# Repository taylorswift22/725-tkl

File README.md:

725-tkl

If you intend to have this produced, please contact me on discord "tamsin." because there are some small adjustments I should make.

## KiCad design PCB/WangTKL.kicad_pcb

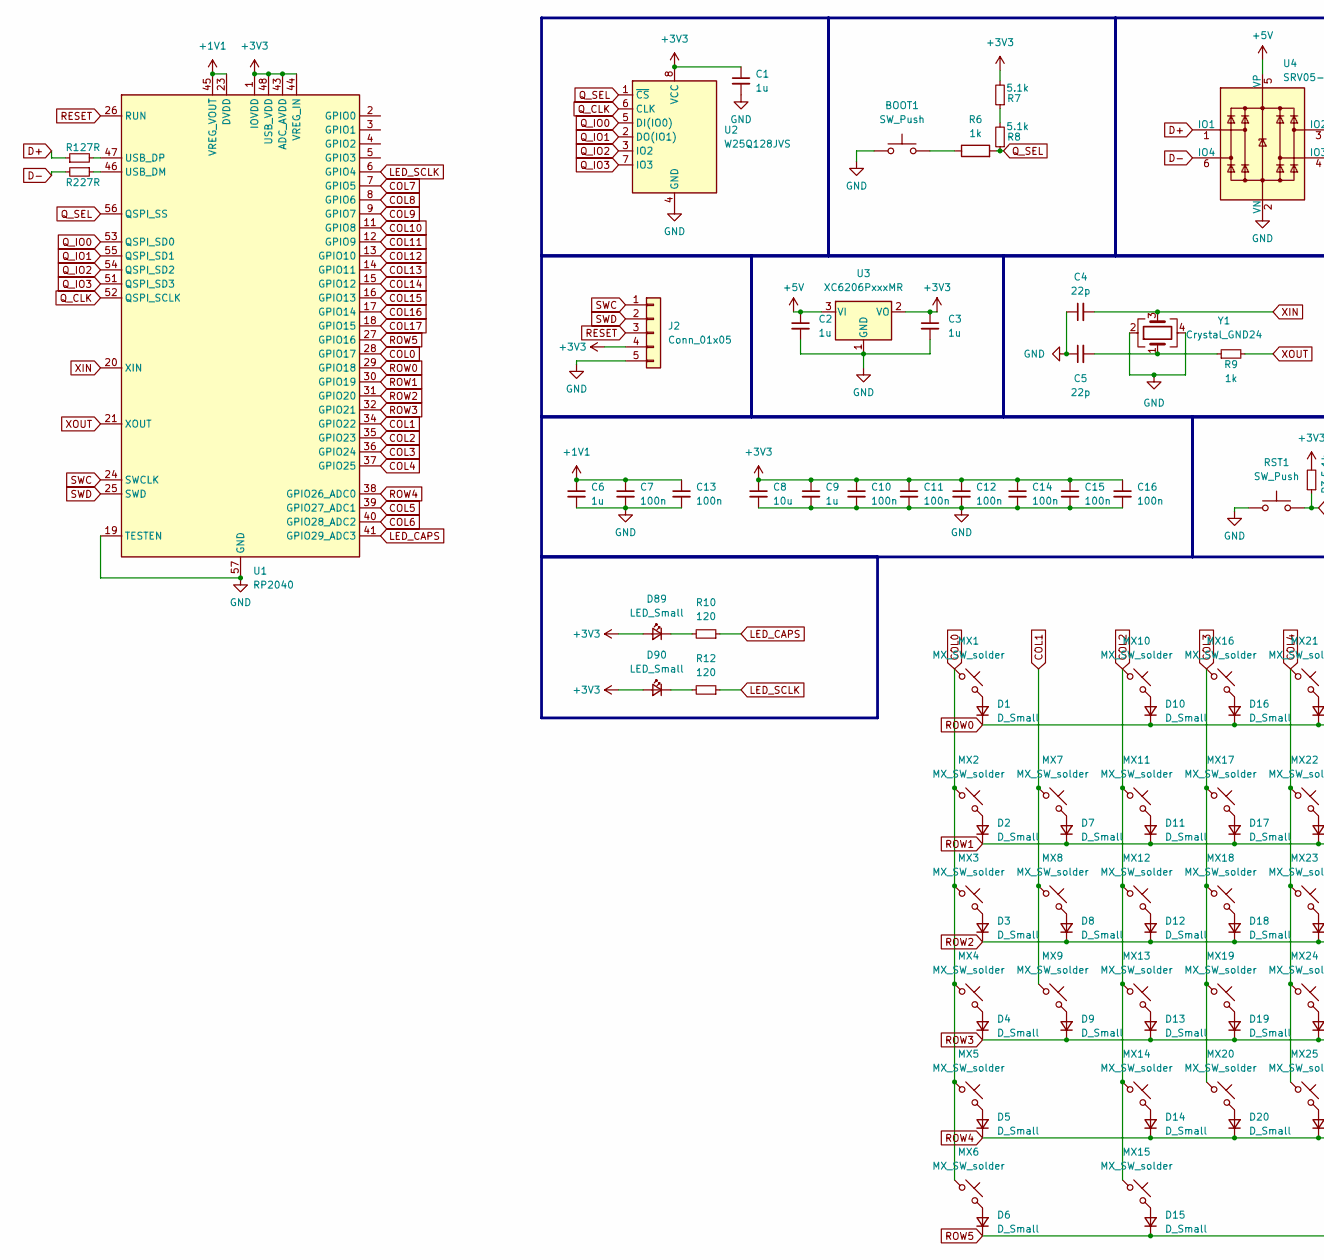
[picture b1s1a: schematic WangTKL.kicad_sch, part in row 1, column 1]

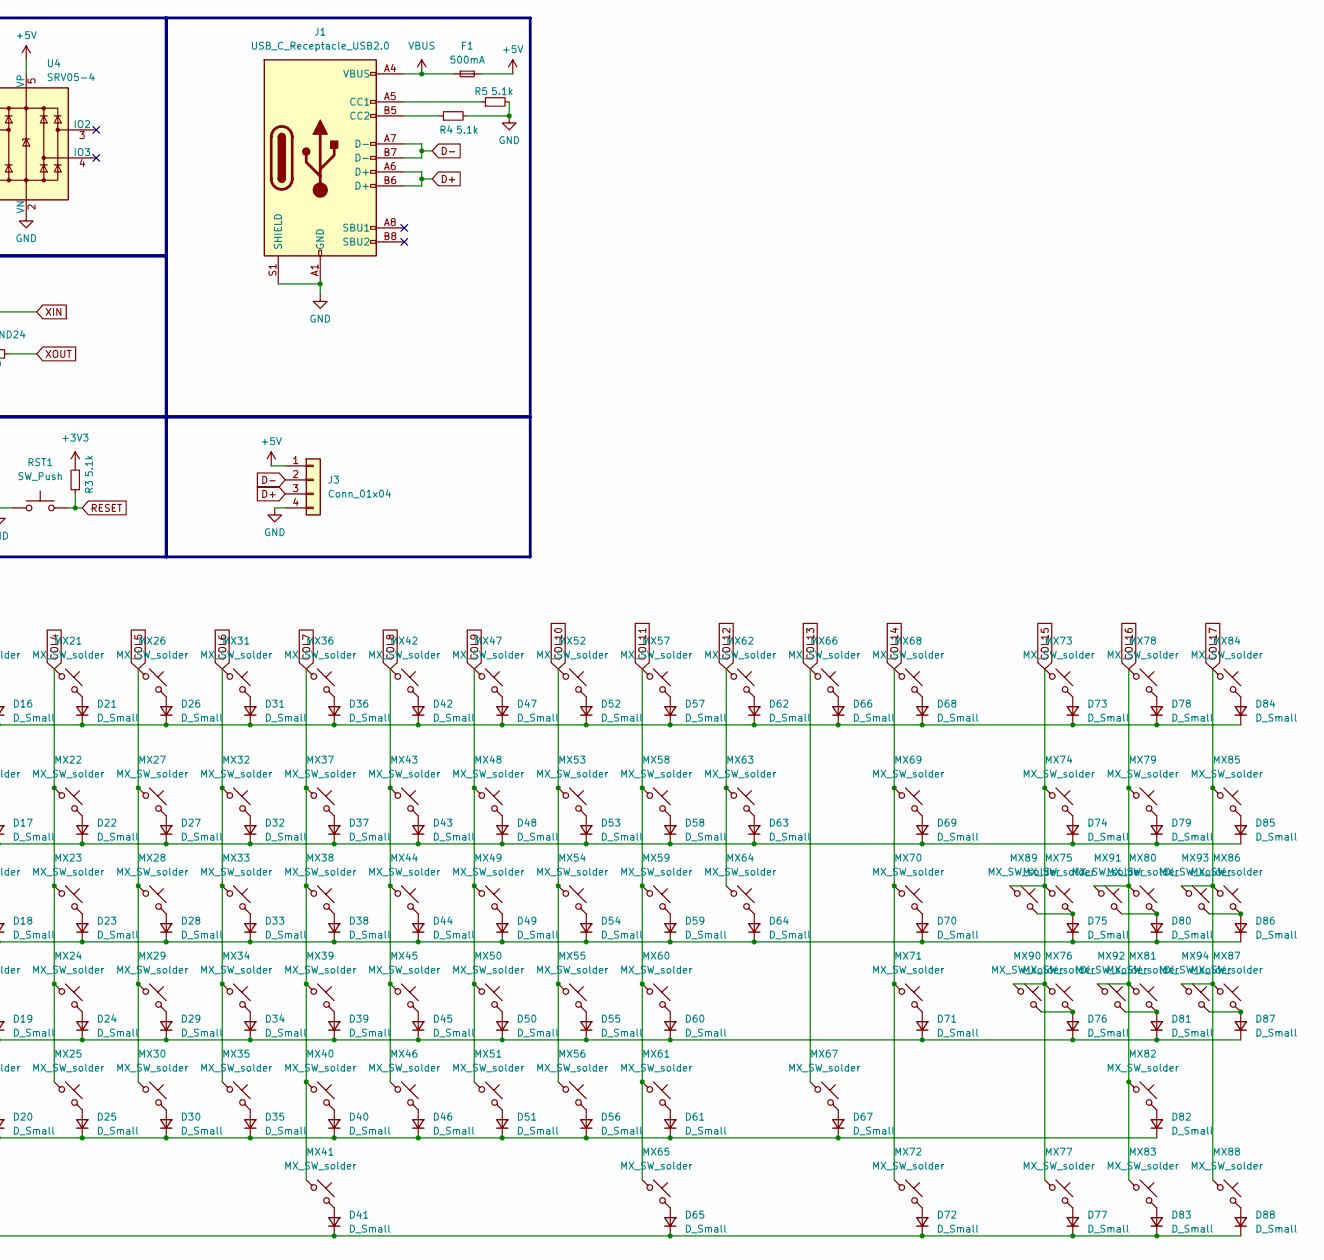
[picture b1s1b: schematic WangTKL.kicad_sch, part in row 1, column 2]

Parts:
BOOT1: SW_Push; SW_SPST_TL3342
C1, C2, C3, C6, C9: 1u; C_0402_1005Metric
C4, C5: 22p; C_0402_1005Metric
C7, C10, C11, C12, C13, C14, C15, C16: 100n; C_0402_1005Metric
C8: 10u; C_0603_1608Metric
D1, D2, D3, D4, D5, D6, D7, D8, D9, D10, D11, D12, D13, D14, D15, D16, D17, D18, D19, D20, D21, D22, D23, D24, D25, D26, D27, D28, D29, D30, D31, D32, D33, D34, D35, D36, D37, D38, D39, D40, D41, D42, D43, D44, D45, D46, D47, D48, D49, D50, D51, D52, D53, D54, D55, D56, D57, D58, D59, D60, D61, D62, D63, D64, D65, D66, D67, D68, D69, D70, D71, D72, D73, D74, D75, D76, D77, D78, D79, D80, D81, D82, D83, D84, D85, D86, D87, D88: D_Small; D_SOD-123
D89, D90: LED_Small; PinHeader_1x02_P2.54mm_Horizontal
F1: 500mA; Fuse_1206_3216Metric
J1: USB_C_Receptacle_USB2.0; USB_C_Receptacle_HRO_TYPE-C-31-M-12
J2: Conn_01x05; PinHeader_1x05_P2.54mm_Vertical
J3: Conn_01x04; Molex_Pico-EZmate_78171-0004_1x04-1MP_P1.20mm_Vertical
MX1, MX2, MX3, MX4, MX5, MX6, MX7, MX8, MX9, MX10, MX11, MX12, MX13, MX14, MX15, MX16, MX17, MX18, MX19, MX20, MX21, MX22, MX23, MX24, MX25, MX26, MX27, MX28, MX29, MX30, MX31, MX32, MX33, MX34, MX35, MX36, MX37, MX38, MX39, MX40, MX41, MX42, MX43, MX44, MX45, MX46, MX47, MX48, MX49, MX50, MX51, MX52, MX53, MX54, MX55, MX56, MX57, MX58, MX59, MX60, MX61, MX62, MX63, MX64, MX65, MX66, MX67, MX68, MX69, MX70, MX71, MX72, MX73, MX74, MX75, MX76, MX77, MX78, MX79, MX80, MX81, MX82, MX83, MX84, MX85, MX86, MX87, MX88, MX89, MX90, MX91, MX92, MX93, MX94: MX_SW_solder; SW_Alps_1u
R1, R2: 27R; R_0402_1005Metric
R3, R4, R5, R7, R8: 5.1k; R_0402_1005Metric
R6, R9: 1k; R_0402_1005Metric
R10, R12: 120; R_0402_1005Metric
RST1: SW_Push; SW_SPST_TL3342
U1: RP2040; QFN-56-1EP_7x7mm_P0.4mm_EP3.2x3.2mm
U2: W25Q128JVS; SOIC-8_5.23x5.23mm_P1.27mm
U3: XC6206PxxxMR; SOT-23-3
U4: SRV05-4; SOT-23-6-routable
Y1: Crystal_GND24; Crystal_SMD_3225-4Pin_3.2x2.5mm

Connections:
+1V1: C6.1, C7.1, C13.1, U1.23 (DVDD), U1.45 (VREG_VOUT), U1.50 (DVDD)
+3V3: C1.1, C3.1, C8.1, C9.1, C10.1, C11.1, C12.1, C14.1, C15.1, C16.1, D89.2 (A), D90.2 (A), J2.4, R3.2, R7.2, U1.1 (IOVDD), U1.10 (IOVDD), U1.22 (IOVDD), U1.33 (IOVDD), U1.42 (IOVDD), U1.43 (ADC_AVDD), U1.44 (VREG_IN), U1.48 (USB_VDD), U1.49 (IOVDD), U2.8 (VCC), U3.2 (VO)
+5V: C2.1, F1.2, J3.1, U3.3 (VI), U4.5 (VP)
COL0: MX1.1, MX2.1, MX3.1, MX4.1, MX5.1, MX6.1, U1.28 (GPIO17)
COL1: MX7.1, MX8.1, MX9.1, U1.34 (GPIO22)
COL2: MX10.1, MX11.1, MX12.1, MX13.1, MX14.1, MX15.1, U1.35 (GPIO23)
COL3: MX16.1, MX17.1, MX18.1, MX19.1, MX20.1, U1.36 (GPIO24)
COL4: MX21.1, MX22.1, MX23.1, MX24.1, MX25.1, U1.37 (GPIO25)
COL5: MX26.1, MX27.1, MX28.1, MX29.1, MX30.1, U1.39 (GPIO27_ADC1)
COL6: MX31.1, MX32.1, MX33.1, MX34.1, MX35.1, U1.40 (GPIO28_ADC2)
COL7: MX36.1, MX37.1, MX38.1, MX39.1, MX40.1, MX41.1, U1.7 (GPIO5)
COL8: MX42.1, MX43.1, MX44.1, MX45.1, MX46.1, U1.8 (GPIO6)
COL9: MX47.1, MX48.1, MX49.1, MX50.1, MX51.1, U1.9 (GPIO7)
COL10: MX52.1, MX53.1, MX54.1, MX55.1, MX56.1, U1.11 (GPIO8)
COL11: MX57.1, MX58.1, MX59.1, MX60.1, MX61.1, MX65.1, U1.12 (GPIO9)
COL12: MX62.1, MX63.1, MX64.1, U1.13 (GPIO10)
COL13: MX66.1, MX67.1, U1.14 (GPIO11)
COL14: MX68.1, MX69.1, MX70.1, MX71.1, MX72.1, U1.15 (GPIO12)
COL15: MX73.1, MX74.1, MX75.1, MX76.1, MX77.1, MX89.1, MX90.1, U1.16 (GPIO13)
COL16: MX78.1, MX79.1, MX80.1, MX81.1, MX82.1, MX83.1, MX91.1, MX92.1, U1.17 (GPIO14)
COL17: MX84.1, MX85.1, MX86.1, MX87.1, MX88.1, MX93.1, MX94.1, U1.18 (GPIO15)
D+: J1.A6 (D+), J1.B6 (D+), J3.3, R1.1, U4.1 (IO1)
D-: J1.A7 (D-), J1.B7 (D-), J3.2, R2.2, U4.6 (IO4)
GND: BOOT1.1, C1.2, C2.2, C3.2, C4.1, C5.1, C6.2, C7.2, C8.2, C9.2, C10.2, C11.2, C12.2, C13.2, C14.2, C15.2, C16.2, J1.A1 (GND), J1.A12 (GND), J1.B1 (GND), J1.B12 (GND), J1.S1 (SHIELD), J2.5, J3.4, R4.2, R5.2, RST1.1, U1.19 (TESTEN), U1.57 (GND), U2.4 (GND), U3.1 (GND), U4.2 (VN), Y1.2, Y1.4
LED_CAPS: R10.1, U1.41 (GPIO29_ADC3)
LED_SCLK: R12.1, U1.6 (GPIO4)
unnamed: BOOT1.2, R6.1
unnamed: C5.2, R9.1, Y1.1
unnamed: D1.2 (A), MX1.2
unnamed: D2.2 (A), MX2.2
unnamed: D3.2 (A), MX3.2
unnamed: D4.2 (A), MX4.2
unnamed: D5.2 (A), MX5.2
unnamed: D6.2 (A), MX6.2
unnamed: D7.2 (A), MX7.2
unnamed: D8.2 (A), MX8.2
unnamed: D9.2 (A), MX9.2
unnamed: D10.2 (A), MX10.2
unnamed: D11.2 (A), MX11.2
unnamed: D12.2 (A), MX12.2
unnamed: D13.2 (A), MX13.2
unnamed: D14.2 (A), MX14.2
unnamed: D15.2 (A), MX15.2
unnamed: D16.2 (A), MX16.2
unnamed: D17.2 (A), MX17.2
unnamed: D18.2 (A), MX18.2
unnamed: D19.2 (A), MX19.2
unnamed: D20.2 (A), MX20.2
unnamed: D21.2 (A), MX21.2
unnamed: D22.2 (A), MX22.2
unnamed: D23.2 (A), MX23.2
unnamed: D24.2 (A), MX24.2
unnamed: D25.2 (A), MX25.2
unnamed: D26.2 (A), MX26.2
unnamed: D27.2 (A), MX27.2
unnamed: D28.2 (A), MX28.2
unnamed: D29.2 (A), MX29.2
unnamed: D30.2 (A), MX30.2
unnamed: D31.2 (A), MX31.2
unnamed: D32.2 (A), MX32.2
unnamed: D33.2 (A), MX33.2
unnamed: D34.2 (A), MX34.2
unnamed: D35.2 (A), MX35.2
unnamed: D36.2 (A), MX36.2
unnamed: D37.2 (A), MX37.2
unnamed: D38.2 (A), MX38.2
unnamed: D39.2 (A), MX39.2
unnamed: D40.2 (A), MX40.2
unnamed: D41.2 (A), MX41.2
unnamed: D42.2 (A), MX42.2
unnamed: D43.2 (A), MX43.2
unnamed: D44.2 (A), MX44.2
unnamed: D45.2 (A), MX45.2
unnamed: D46.2 (A), MX46.2
unnamed: D47.2 (A), MX47.2
unnamed: D48.2 (A), MX48.2
unnamed: D49.2 (A), MX49.2
unnamed: D50.2 (A), MX50.2
unnamed: D51.2 (A), MX51.2
unnamed: D52.2 (A), MX52.2
unnamed: D53.2 (A), MX53.2
unnamed: D54.2 (A), MX54.2
unnamed: D55.2 (A), MX55.2
unnamed: D56.2 (A), MX56.2
unnamed: D57.2 (A), MX57.2
unnamed: D58.2 (A), MX58.2
unnamed: D59.2 (A), MX59.2
unnamed: D60.2 (A), MX60.2
unnamed: D61.2 (A), MX61.2
unnamed: D62.2 (A), MX62.2
unnamed: D63.2 (A), MX63.2
unnamed: D64.2 (A), MX64.2
unnamed: D65.2 (A), MX65.2
unnamed: D66.2 (A), MX66.2
unnamed: D67.2 (A), MX67.2
unnamed: D68.2 (A), MX68.2
unnamed: D69.2 (A), MX69.2
unnamed: D70.2 (A), MX70.2
unnamed: D71.2 (A), MX71.2
unnamed: D72.2 (A), MX72.2
unnamed: D73.2 (A), MX73.2
unnamed: D74.2 (A), MX74.2
unnamed: D75.2 (A), MX75.2, MX89.2
unnamed: D76.2 (A), MX76.2, MX90.2
unnamed: D77.2 (A), MX77.2
unnamed: D78.2 (A), MX78.2
unnamed: D79.2 (A), MX79.2
unnamed: D80.2 (A), MX80.2, MX91.2
unnamed: D81.2 (A), MX81.2, MX92.2
unnamed: D82.2 (A), MX82.2
unnamed: D83.2 (A), MX83.2
unnamed: D84.2 (A), MX84.2
unnamed: D85.2 (A), MX85.2
unnamed: D86.2 (A), MX86.2, MX93.2
unnamed: D87.2 (A), MX87.2, MX94.2
unnamed: D88.2 (A), MX88.2
unnamed: D89.1 (K), R10.2
unnamed: D90.1 (K), R12.2
unnamed: J1.A5 (CC1), R5.1
unnamed: J1.B5 (CC2), R4.1
unnamed: R7.1, R8.2
unnamed: R2.1, U1.46 (USB_DM)
unnamed: R1.2, U1.47 (USB_DP)
Q_CLK: U1.52 (QSPI_SCLK), U2.6 (CLK)
Q_IO0: U1.53 (QSPI_SD0), U2.5 (DI(IO0))
Q_IO1: U1.55 (QSPI_SD1), U2.2 (DO(IO1))
Q_IO2: U1.54 (QSPI_SD2), U2.3 (IO2)
Q_IO3: U1.51 (QSPI_SD3), U2.7 (IO3)
Q_SEL: R6.2, R8.1, U1.56 (QSPI_SS), U2.1 (~CS)
RESET: J2.3, R3.1, RST1.2, U1.26 (RUN)
ROW0: D1.1 (K), D10.1 (K), D16.1 (K), D21.1 (K), D26.1 (K), D31.1 (K), D36.1 (K), D42.1 (K), D47.1 (K), D52.1 (K), D57.1 (K), D62.1 (K), D66.1 (K), D68.1 (K), D73.1 (K), D78.1 (K), D84.1 (K), U1.29 (GPIO18)
ROW1: D2.1 (K), D7.1 (K), D11.1 (K), D17.1 (K), D22.1 (K), D27.1 (K), D32.1 (K), D37.1 (K), D43.1 (K), D48.1 (K), D53.1 (K), D58.1 (K), D63.1 (K), D69.1 (K), D74.1 (K), D79.1 (K), D85.1 (K), U1.30 (GPIO19)
ROW2: D3.1 (K), D8.1 (K), D12.1 (K), D18.1 (K), D23.1 (K), D28.1 (K), D33.1 (K), D38.1 (K), D44.1 (K), D49.1 (K), D54.1 (K), D59.1 (K), D64.1 (K), D70.1 (K), D75.1 (K), D80.1 (K), D86.1 (K), U1.31 (GPIO20)
ROW3: D4.1 (K), D9.1 (K), D13.1 (K), D19.1 (K), D24.1 (K), D29.1 (K), D34.1 (K), D39.1 (K), D45.1 (K), D50.1 (K), D55.1 (K), D60.1 (K), D71.1 (K), D76.1 (K), D81.1 (K), D87.1 (K), U1.32 (GPIO21)
ROW4: D5.1 (K), D14.1 (K), D20.1 (K), D25.1 (K), D30.1 (K), D35.1 (K), D40.1 (K), D46.1 (K), D51.1 (K), D56.1 (K), D61.1 (K), D67.1 (K), D82.1 (K), U1.38 (GPIO26_ADC0)
ROW5: D6.1 (K), D15.1 (K), D41.1 (K), D65.1 (K), D72.1 (K), D77.1 (K), D83.1 (K), D88.1 (K), U1.27 (GPIO16)
SWC: J2.1, U1.24 (SWCLK)
SWD: J2.2, U1.25 (SWD)
VBUS: F1.1, J1.A4 (VBUS), J1.A9 (VBUS), J1.B4 (VBUS), J1.B9 (VBUS)
XIN: C4.2, U1.20 (XIN), Y1.3
XOUT: R9.2, U1.21 (XOUT)

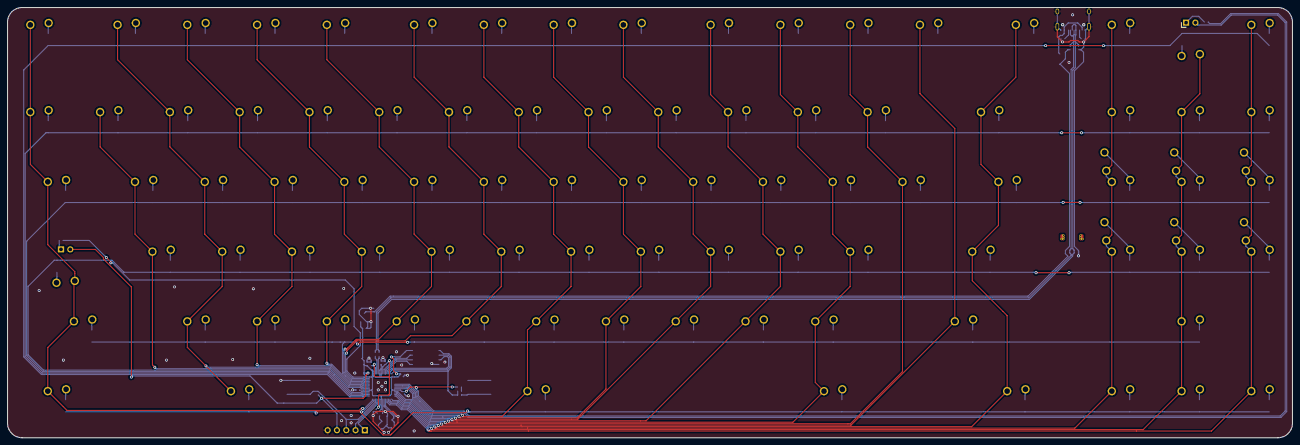
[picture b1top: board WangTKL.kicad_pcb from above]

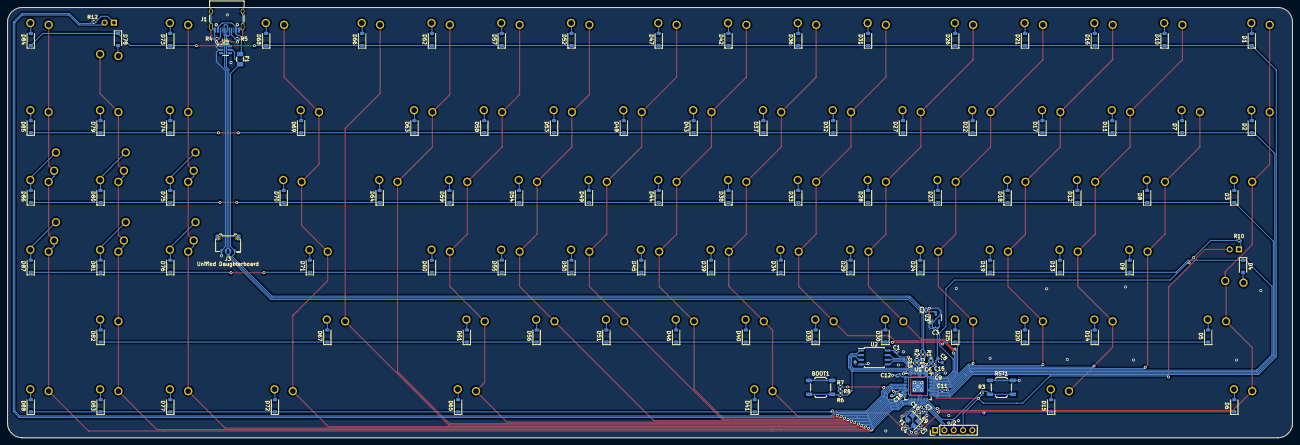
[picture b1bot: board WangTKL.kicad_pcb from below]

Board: 2 copper layers, 350.8 x 117.5 mm, 222 parts (126 on the bottom side), 141 nets.

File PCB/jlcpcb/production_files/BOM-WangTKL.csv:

Comment,Designator,Footprint,LCSC
1k,"R6,R9",R_0402_1005Metric,C11702
W25Q128JVS,U2,SOIC-8_5.23x5.23mm_P1.27mm,C131025
27R,"R1,R2",R_0402_1005Metric,C138021
22p,"C4,C5",C_0402_1005Metric,C1555
10u,C8,C_0603_1608Metric,C19702
RP2040,U1,QFN-56-1EP_7x7mm_P0.4mm_EP3.2x3.2mm,C2040
120,"R10,R12",R_0402_1005Metric,C25079
5.1k,"R3,R4,R5,R7,R8",R_0402_1005Metric,C25905
100n,"C10,C11,C12,C13,C14,C15,C16,C7",C_0402_1005Metric,C307331
SW_Push,"BOOT1,RST1",SW_SPST_TL3342,C318884
Conn_01x04,J3,Molex_Pico-EZmate_78171-0004_1x04-1MP_P1.20mm_Vertical,C528030
1u,"C1,C2,C3,C6,C9",C_0402_1005Metric,C52923
XC6206PxxxMR,U3,SOT-23-3,C5446
500mA,F1,Fuse_1206_3216Metric,C70076
D_Small,"D1,D10,D11,D12,D13,D14,D15,D16,D17,D18,D19,D2,D20,D21,D22,D23,D24,D25,D26,D27,D28,D29,D3,D30,D31,D32,D33,D34,D35,D36,D37,D38,D39,D4,D40,D41,D42,D43,D44,D45,D46,D47,D48,D49,D5,D50,D51,D52,D53,D54,D55,D56,D57,D58,D59,D6,D60,D61,D62,D63,D64,D65,D66,D67,D68,D69,D7,D70,D71,D72,D73,D74,D75,D76,D77,D78,D79,D8,D80,D81,D82,D83,D84,D85,D86,D87,D88,D9",D_SOD-123,C81598
SRV05-4,U4,SOT-23-6-routable,C85364
Crystal_GND24,Y1,Crystal_SMD_3225-4Pin_3.2x2.5mm,C9002

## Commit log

2024-04-27 Add Files
